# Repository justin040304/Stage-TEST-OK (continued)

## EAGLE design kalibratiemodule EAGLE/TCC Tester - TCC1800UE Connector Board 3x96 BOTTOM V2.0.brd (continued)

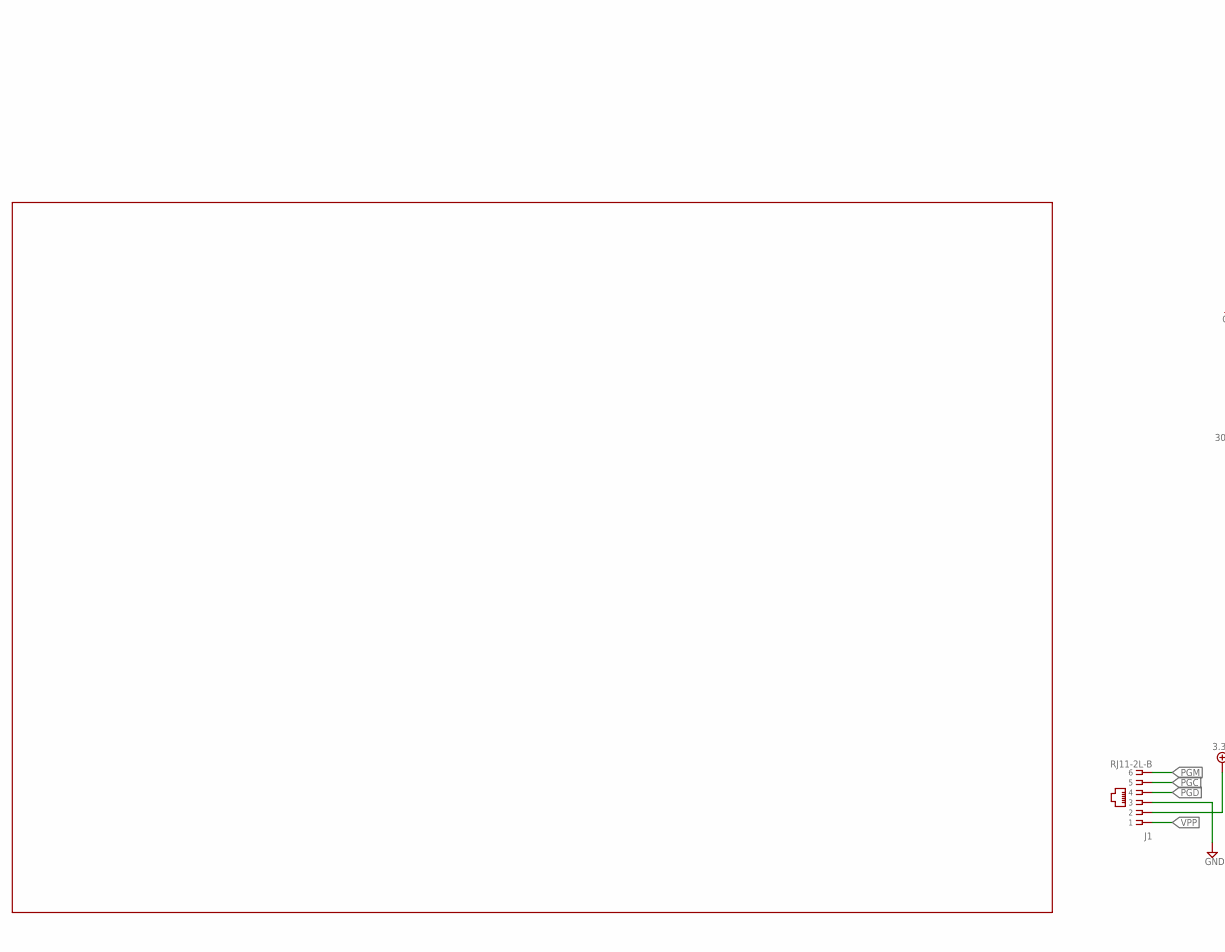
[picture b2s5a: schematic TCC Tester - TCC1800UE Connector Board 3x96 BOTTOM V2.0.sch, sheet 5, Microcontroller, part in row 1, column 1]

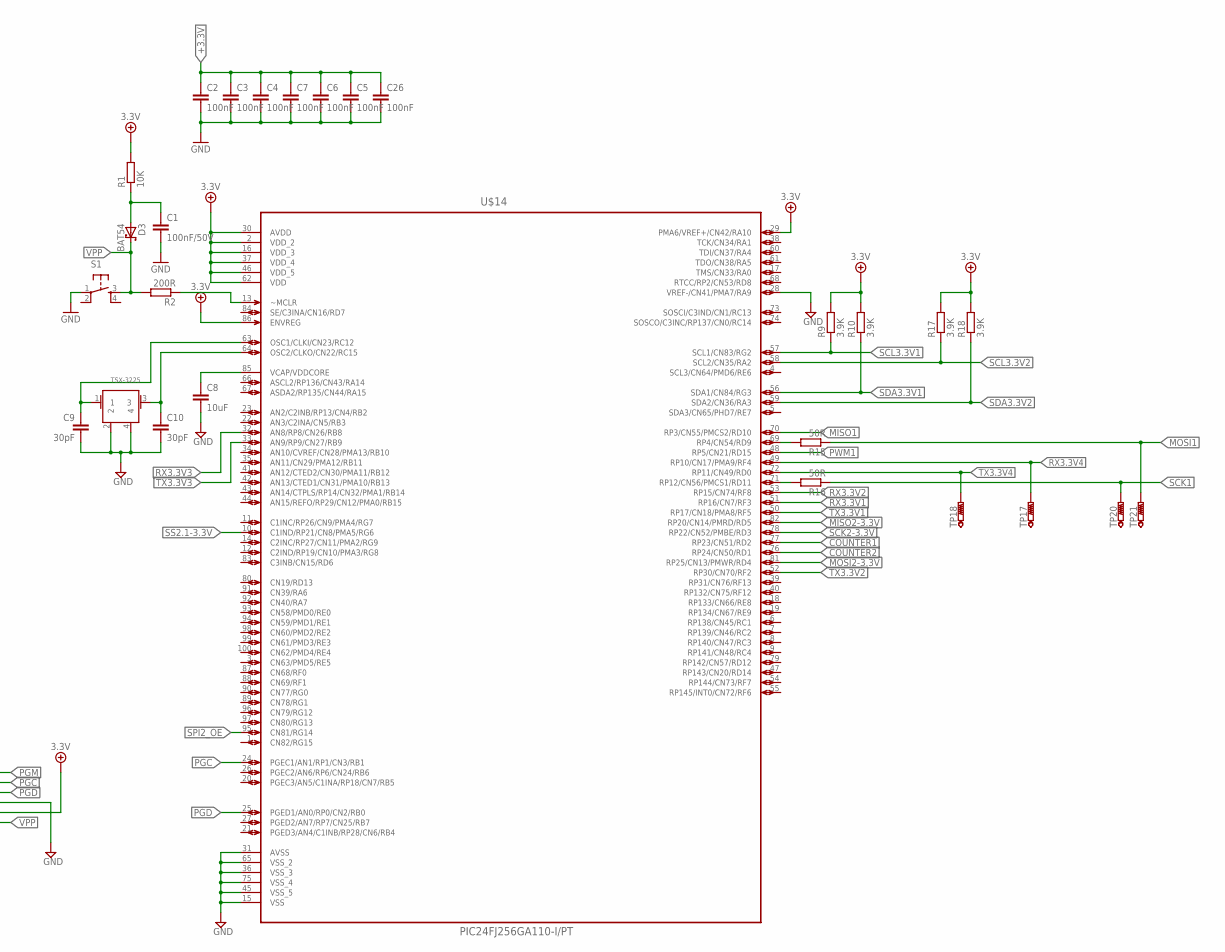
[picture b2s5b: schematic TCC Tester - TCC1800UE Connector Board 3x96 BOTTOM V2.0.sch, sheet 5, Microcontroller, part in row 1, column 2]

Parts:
C1: 100nF/50V; C0603
C2, C3, C4, C5, C6, C7, C26: 100nF; C0603
C8: 10uF; C0603
C9, C10: 30pF; C0603
D3: BAT54; SOT23
J1: RJ11-2L-B; RJ11-NO_SHIELD
R1: 10K; R0603
R2: 200R; R0603
R9, R10, R17, R18: 3.9K; R0603
R15, R16: 50R; R0603
S1: TAC_SWITCHPTH; TACTILE-PTH
TP17, TP18, TP20, TP21: PTR1TP13R; TP13R
U$14: PIC24FJ256GA110-I/PT; QFP40P1400X1400X120-100N
U$15: TSX-3225; SMD,3.2MM_X_2.5MM

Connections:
+3.3V: C2.1, C3.1, C4.1, C5.1, C6.1, C7.1, C26.1, J1.2, R1.2, R9.2, R10.2, R17.2, R18.2, U$14.2 (VDD_2), U$14.16 (VDD_3), U$14.29 (PMA6/VREF+/CN42/RA10), U$14.30 (AVDD), U$14.37 (VDD_4), U$14.46 (VDD_5), U$14.62 (VDD), U$14.86 (ENVREG); also elsewhere on the board
COUNTER1: U$14.77 (RP23/CN51/RD2); also elsewhere on the board
COUNTER2: U$14.76 (RP24/CN50/RD1); also elsewhere on the board
GND: C1.2, C2.2, C3.2, C4.2, C5.2, C6.2, C7.2, C8.2, C9.2, C10.2, C26.2, J1.3, S1.1, U$14.15 (VSS), U$14.28 (VREF-/CN41/PMA7/RA9), U$14.31 (AVSS), U$14.36 (VSS_3), U$14.45 (VSS_5), U$14.65 (VSS_2), U$14.75 (VSS_4), U$15.2, U$15.4; also elsewhere on the board
MISO1: U$14.70 (RP3/CN55/PMCS2/RD10)
MISO2-3.3V: U$14.82 (RP20/CN14/PMRD/RD5); also elsewhere on the board
MOSI1: R15.1, TP21.TP; also elsewhere on the board
MOSI2-3.3V: U$14.81 (RP25/CN13/PMWR/RD4); also elsewhere on the board
unnamed: R15.2, U$14.69 (RP4/CN54/RD9)
unnamed: R16.2, U$14.71 (RP12/CN56/PMCS1/RD11)
unnamed: C1.1, D3.1 (A), R1.1
unnamed: R2.1, U$14.13 (~MCLR)
unnamed: C9.1, U$14.63 (OSC1/CLKI/CN23/RC12), U$15.1
unnamed: C10.1, U$14.64 (OSC2/CLKO/CN22/RC15), U$15.3
unnamed: C8.1, U$14.85 (VCAP/VDDCORE)
PGC: J1.5, U$14.24 (PGEC1/AN1/RP1/CN3/RB1)
PGD: J1.4, U$14.25 (PGED1/AN0/RP0/CN2/RB0)
PGM: J1.6
PWM1: U$14.48 (RP5/CN21/RD15); also elsewhere on the board
RX3.3V1: U$14.51 (RP16/CN7/RF3); also elsewhere on the board
RX3.3V2: U$14.53 (RP15/CN74/RF8); also elsewhere on the board
RX3.3V3: U$14.32 (AN8/RP8/CN26/RB8); also elsewhere on the board
RX3.3V4: TP17.TP, U$14.49 (RP10/CN17/PMA9/RF4)
SCK1: R16.1, TP20.TP; also elsewhere on the board
SCK2-3.3V: U$14.78 (RP22/CN52/PMBE/RD3); also elsewhere on the board
SCL3.3V1: R9.1, U$14.57 (SCL1/CN83/RG2); also elsewhere on the board
SCL3.3V2: R17.1, U$14.58 (SCL2/CN35/RA2); also elsewhere on the board
SDA3.3V1: R10.1, U$14.56 (SDA1/CN84/RG3); also elsewhere on the board
SDA3.3V2: R18.1, U$14.59 (SDA2/CN36/RA3); also elsewhere on the board
SPI2_OE: U$14.95 (CN81/RG14); also elsewhere on the board
SS2.1-3.3V: U$14.10 (C1IND/RP21/CN8/PMA5/RG6); also elsewhere on the board
TX3.3V1: U$14.50 (RP17/CN18/PMA8/RF5); also elsewhere on the board
TX3.3V2: U$14.52 (RP30/CN70/RF2); also elsewhere on the board
TX3.3V3: U$14.33 (AN9/RP9/CN27/RB9); also elsewhere on the board
TX3.3V4: TP18.TP, U$14.72 (RP11/CN49/RD0)
VPP: D3.3 (C), J1.1, R2.2, S1.3

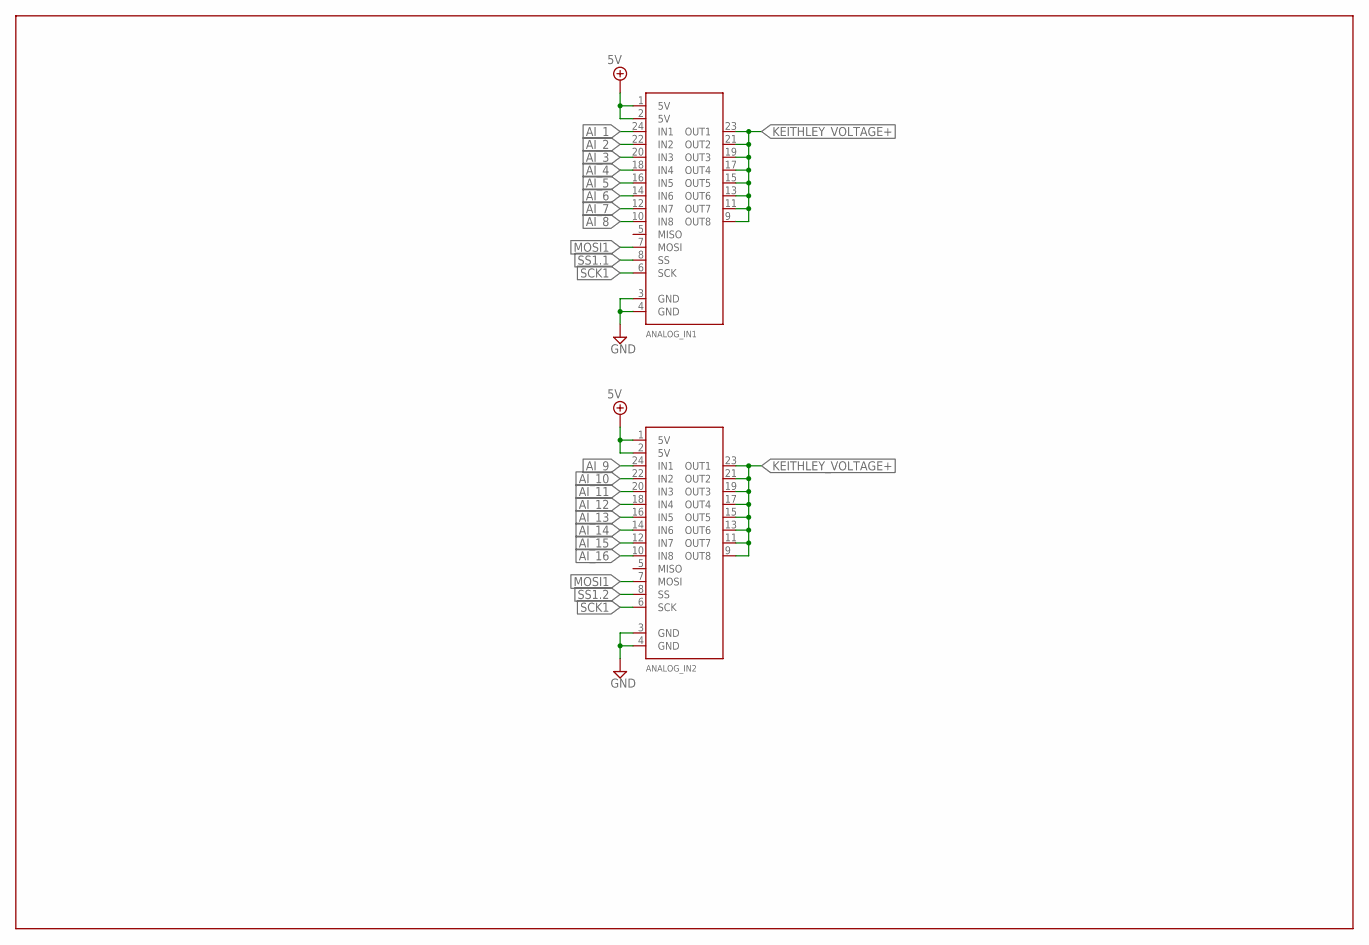
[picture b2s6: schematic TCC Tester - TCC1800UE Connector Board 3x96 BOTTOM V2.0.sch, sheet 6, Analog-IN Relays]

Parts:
ANALOG_IN1, ANALOG_IN2: RELAY_BOARD_SOCKET

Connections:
5V: ANALOG_IN1.1 (5V), ANALOG_IN1.2 (5V), ANALOG_IN2.1 (5V), ANALOG_IN2.2 (5V); also elsewhere on the board
AI_1: ANALOG_IN1.24 (IN1); also elsewhere on the board
AI_2: ANALOG_IN1.22 (IN2); also elsewhere on the board
AI_3: ANALOG_IN1.20 (IN3); also elsewhere on the board
AI_4: ANALOG_IN1.18 (IN4); also elsewhere on the board
AI_5: ANALOG_IN1.16 (IN5); also elsewhere on the board
AI_6: ANALOG_IN1.14 (IN6); also elsewhere on the board
AI_7: ANALOG_IN1.12 (IN7); also elsewhere on the board
AI_8: ANALOG_IN1.10 (IN8); also elsewhere on the board
AI_9: ANALOG_IN2.24 (IN1); also elsewhere on the board
AI_10: ANALOG_IN2.22 (IN2); also elsewhere on the board
AI_11: ANALOG_IN2.20 (IN3); also elsewhere on the board
AI_12: ANALOG_IN2.18 (IN4); also elsewhere on the board
AI_13: ANALOG_IN2.16 (IN5); also elsewhere on the board
AI_14: ANALOG_IN2.14 (IN6); also elsewhere on the board
AI_15: ANALOG_IN2.12 (IN7); also elsewhere on the board
AI_16: ANALOG_IN2.10 (IN8); also elsewhere on the board
GND: ANALOG_IN1.3 (GND), ANALOG_IN1.4 (GND), ANALOG_IN2.3 (GND), ANALOG_IN2.4 (GND); also elsewhere on the board
KEITHLEY_VOLTAGE+: ANALOG_IN1.9 (OUT8), ANALOG_IN1.11 (OUT7), ANALOG_IN1.13 (OUT6), ANALOG_IN1.15 (OUT5), ANALOG_IN1.17 (OUT4), ANALOG_IN1.19 (OUT3), ANALOG_IN1.21 (OUT2), ANALOG_IN1.23 (OUT1), ANALOG_IN2.9 (OUT8), ANALOG_IN2.11 (OUT7), ANALOG_IN2.13 (OUT6), ANALOG_IN2.15 (OUT5), ANALOG_IN2.17 (OUT4), ANALOG_IN2.19 (OUT3), ANALOG_IN2.21 (OUT2), ANALOG_IN2.23 (OUT1); also elsewhere on the board
MOSI1: ANALOG_IN1.7 (MOSI), ANALOG_IN2.7 (MOSI); also elsewhere on the board
SCK1: ANALOG_IN1.6 (SCK), ANALOG_IN2.6 (SCK); also elsewhere on the board
SS1.1: ANALOG_IN1.8 (SS); also elsewhere on the board
SS1.2: ANALOG_IN2.8 (SS); also elsewhere on the board

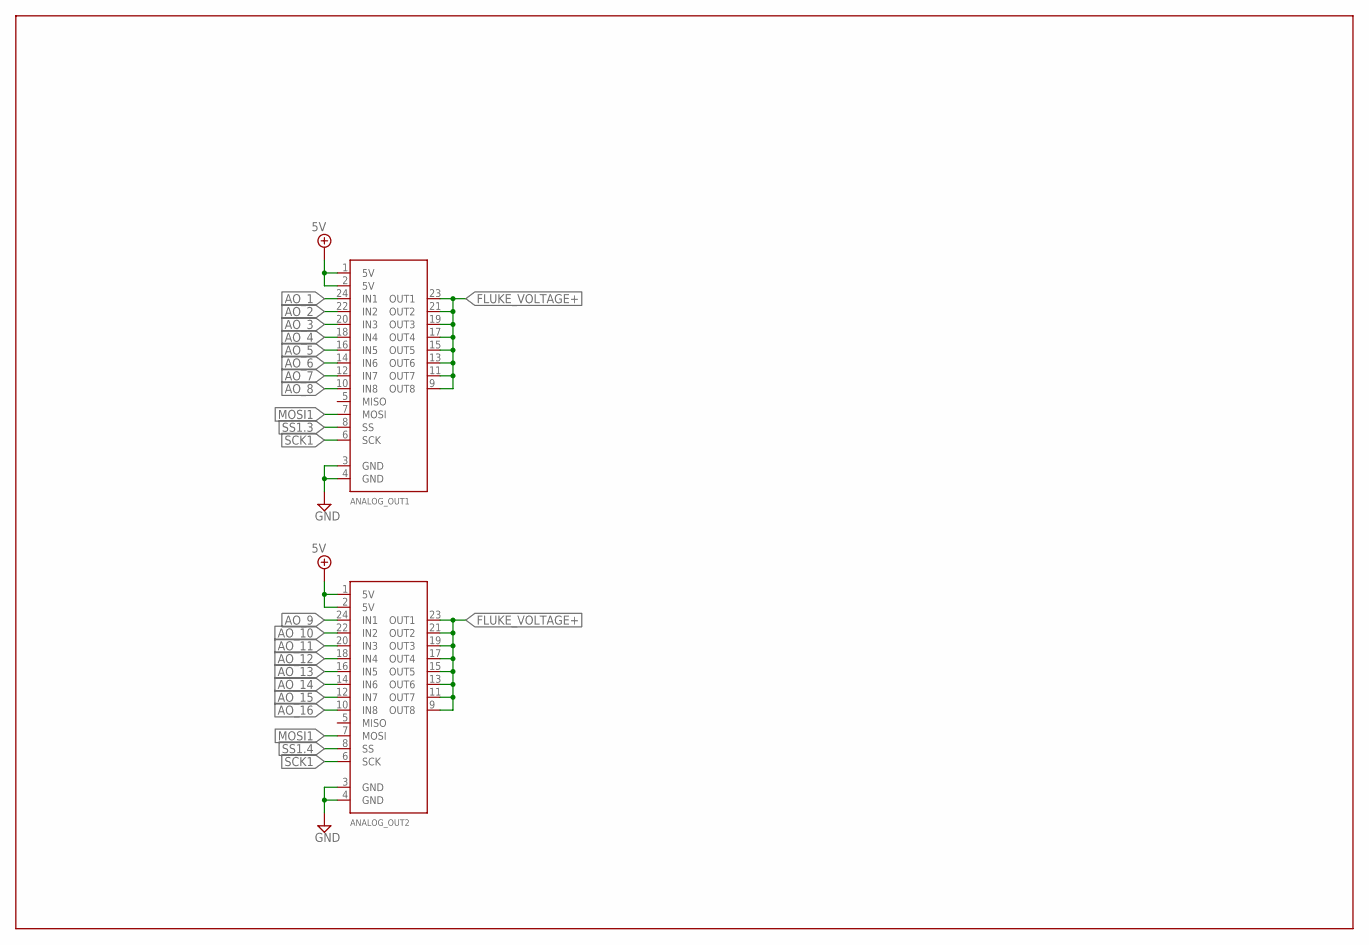
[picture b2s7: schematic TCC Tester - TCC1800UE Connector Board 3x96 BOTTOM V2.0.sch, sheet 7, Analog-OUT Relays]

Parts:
ANALOG_OUT1, ANALOG_OUT2: RELAY_BOARD_SOCKET

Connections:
5V: ANALOG_OUT1.1 (5V), ANALOG_OUT1.2 (5V), ANALOG_OUT2.1 (5V), ANALOG_OUT2.2 (5V); also elsewhere on the board
AO_1: ANALOG_OUT1.24 (IN1); also elsewhere on the board
AO_2: ANALOG_OUT1.22 (IN2); also elsewhere on the board
AO_3: ANALOG_OUT1.20 (IN3); also elsewhere on the board
AO_4: ANALOG_OUT1.18 (IN4); also elsewhere on the board
AO_5: ANALOG_OUT1.16 (IN5); also elsewhere on the board
AO_6: ANALOG_OUT1.14 (IN6); also elsewhere on the board
AO_7: ANALOG_OUT1.12 (IN7); also elsewhere on the board
AO_8: ANALOG_OUT1.10 (IN8); also elsewhere on the board
AO_9: ANALOG_OUT2.24 (IN1); also elsewhere on the board
AO_10: ANALOG_OUT2.22 (IN2); also elsewhere on the board
AO_11: ANALOG_OUT2.20 (IN3); also elsewhere on the board
AO_12: ANALOG_OUT2.18 (IN4); also elsewhere on the board
AO_13: ANALOG_OUT2.16 (IN5); also elsewhere on the board
AO_14: ANALOG_OUT2.14 (IN6); also elsewhere on the board
AO_15: ANALOG_OUT2.12 (IN7); also elsewhere on the board
AO_16: ANALOG_OUT2.10 (IN8); also elsewhere on the board
FLUKE_VOLTAGE+: ANALOG_OUT1.9 (OUT8), ANALOG_OUT1.11 (OUT7), ANALOG_OUT1.13 (OUT6), ANALOG_OUT1.15 (OUT5), ANALOG_OUT1.17 (OUT4), ANALOG_OUT1.19 (OUT3), ANALOG_OUT1.21 (OUT2), ANALOG_OUT1.23 (OUT1), ANALOG_OUT2.9 (OUT8), ANALOG_OUT2.11 (OUT7), ANALOG_OUT2.13 (OUT6), ANALOG_OUT2.15 (OUT5), ANALOG_OUT2.17 (OUT4), ANALOG_OUT2.19 (OUT3), ANALOG_OUT2.21 (OUT2), ANALOG_OUT2.23 (OUT1); also elsewhere on the board
GND: ANALOG_OUT1.3 (GND), ANALOG_OUT1.4 (GND), ANALOG_OUT2.3 (GND), ANALOG_OUT2.4 (GND); also elsewhere on the board
MOSI1: ANALOG_OUT1.7 (MOSI), ANALOG_OUT2.7 (MOSI); also elsewhere on the board
SCK1: ANALOG_OUT1.6 (SCK), ANALOG_OUT2.6 (SCK); also elsewhere on the board
SS1.3: ANALOG_OUT1.8 (SS); also elsewhere on the board
SS1.4: ANALOG_OUT2.8 (SS); also elsewhere on the board

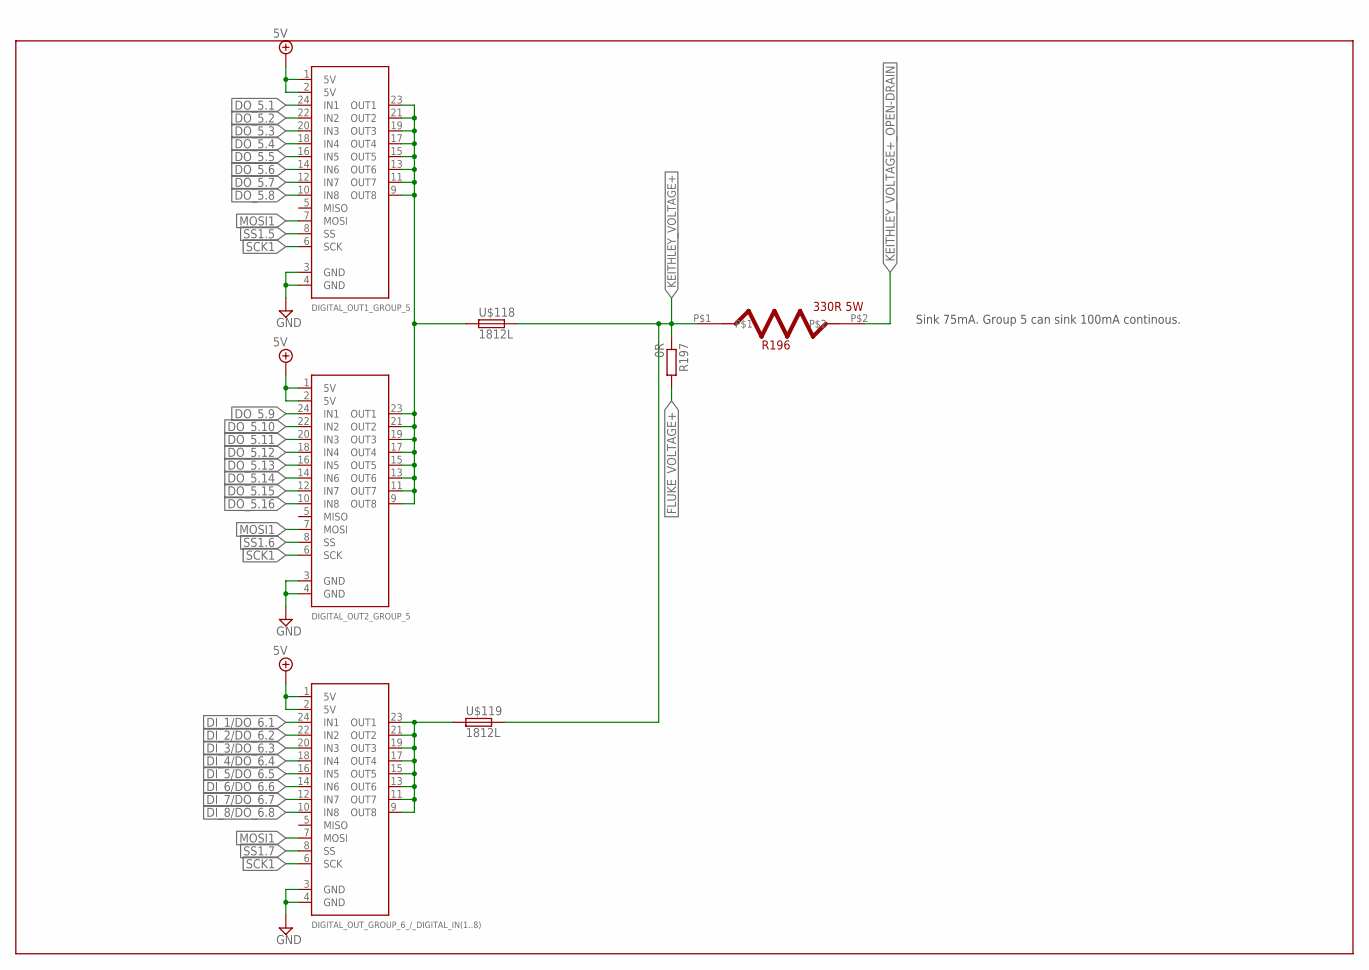
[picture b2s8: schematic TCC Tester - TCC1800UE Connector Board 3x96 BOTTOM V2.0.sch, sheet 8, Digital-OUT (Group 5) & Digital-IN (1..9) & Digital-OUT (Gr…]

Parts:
DIGITAL_OUT1_GROUP_5, DIGITAL_OUT2_GROUP_5: RELAY_BOARD_SOCKET
DIGITAL_OUT_GROUP_6_/_DIGITAL_IN(1..8): RELAY_BOARD_SOCKET
R196: 330R 5W; SMW5220RJT
R197: 0R; R0603
U$118, U$119: 1812L

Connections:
5V: DIGITAL_OUT1_GROUP_5.1 (5V), DIGITAL_OUT1_GROUP_5.2 (5V), DIGITAL_OUT2_GROUP_5.1 (5V), DIGITAL_OUT2_GROUP_5.2 (5V), DIGITAL_OUT_GROUP_6_/_DIGITAL_IN(1..8).1 (5V), DIGITAL_OUT_GROUP_6_/_DIGITAL_IN(1..8).2 (5V); also elsewhere on the board
DI_1/DO_6.1: DIGITAL_OUT_GROUP_6_/_DIGITAL_IN(1..8).24 (IN1); also elsewhere on the board
DI_2/DO_6.2: DIGITAL_OUT_GROUP_6_/_DIGITAL_IN(1..8).22 (IN2); also elsewhere on the board
DI_3/DO_6.3: DIGITAL_OUT_GROUP_6_/_DIGITAL_IN(1..8).20 (IN3); also elsewhere on the board
DI_4/DO_6.4: DIGITAL_OUT_GROUP_6_/_DIGITAL_IN(1..8).18 (IN4); also elsewhere on the board
DI_5/DO_6.5: DIGITAL_OUT_GROUP_6_/_DIGITAL_IN(1..8).16 (IN5); also elsewhere on the board
DI_6/DO_6.6: DIGITAL_OUT_GROUP_6_/_DIGITAL_IN(1..8).14 (IN6); also elsewhere on the board
DI_7/DO_6.7: DIGITAL_OUT_GROUP_6_/_DIGITAL_IN(1..8).12 (IN7); also elsewhere on the board
DI_8/DO_6.8: DIGITAL_OUT_GROUP_6_/_DIGITAL_IN(1..8).10 (IN8); also elsewhere on the board
DO_5.1: DIGITAL_OUT1_GROUP_5.24 (IN1); also elsewhere on the board
DO_5.2: DIGITAL_OUT1_GROUP_5.22 (IN2); also elsewhere on the board
DO_5.3: DIGITAL_OUT1_GROUP_5.20 (IN3); also elsewhere on the board
DO_5.4: DIGITAL_OUT1_GROUP_5.18 (IN4); also elsewhere on the board
DO_5.5: DIGITAL_OUT1_GROUP_5.16 (IN5); also elsewhere on the board
DO_5.6: DIGITAL_OUT1_GROUP_5.14 (IN6); also elsewhere on the board
DO_5.7: DIGITAL_OUT1_GROUP_5.12 (IN7); also elsewhere on the board
DO_5.8: DIGITAL_OUT1_GROUP_5.10 (IN8); also elsewhere on the board
DO_5.9: DIGITAL_OUT2_GROUP_5.24 (IN1); also elsewhere on the board
DO_5.10: DIGITAL_OUT2_GROUP_5.22 (IN2); also elsewhere on the board
DO_5.11: DIGITAL_OUT2_GROUP_5.20 (IN3); also elsewhere on the board
DO_5.12: DIGITAL_OUT2_GROUP_5.18 (IN4); also elsewhere on the board
DO_5.13: DIGITAL_OUT2_GROUP_5.16 (IN5); also elsewhere on the board
DO_5.14: DIGITAL_OUT2_GROUP_5.14 (IN6); also elsewhere on the board
DO_5.15: DIGITAL_OUT2_GROUP_5.12 (IN7); also elsewhere on the board
DO_5.16: DIGITAL_OUT2_GROUP_5.10 (IN8); also elsewhere on the board
FLUKE_VOLTAGE+: R197.2; also elsewhere on the board
GND: DIGITAL_OUT1_GROUP_5.3 (GND), DIGITAL_OUT1_GROUP_5.4 (GND), DIGITAL_OUT2_GROUP_5.3 (GND), DIGITAL_OUT2_GROUP_5.4 (GND), DIGITAL_OUT_GROUP_6_/_DIGITAL_IN(1..8).3 (GND), DIGITAL_OUT_GROUP_6_/_DIGITAL_IN(1..8).4 (GND); also elsewhere on the board
KEITHLEY_VOLTAGE+: R196.P$1, R197.1, U$118.P$2 (2), U$119.P$2 (2); also elsewhere on the board
KEITHLEY_VOLTAGE+_OPEN-DRAIN: R196.P$2; also elsewhere on the board
MOSI1: DIGITAL_OUT1_GROUP_5.7 (MOSI), DIGITAL_OUT2_GROUP_5.7 (MOSI), DIGITAL_OUT_GROUP_6_/_DIGITAL_IN(1..8).7 (MOSI); also elsewhere on the board
unnamed: DIGITAL_OUT1_GROUP_5.9 (OUT8), DIGITAL_OUT1_GROUP_5.11 (OUT7), DIGITAL_OUT1_GROUP_5.13 (OUT6), DIGITAL_OUT1_GROUP_5.15 (OUT5), DIGITAL_OUT1_GROUP_5.17 (OUT4), DIGITAL_OUT1_GROUP_5.19 (OUT3), DIGITAL_OUT1_GROUP_5.21 (OUT2), DIGITAL_OUT1_GROUP_5.23 (OUT1), DIGITAL_OUT2_GROUP_5.9 (OUT8), DIGITAL_OUT2_GROUP_5.11 (OUT7), DIGITAL_OUT2_GROUP_5.13 (OUT6), DIGITAL_OUT2_GROUP_5.15 (OUT5), DIGITAL_OUT2_GROUP_5.17 (OUT4), DIGITAL_OUT2_GROUP_5.19 (OUT3), DIGITAL_OUT2_GROUP_5.21 (OUT2), DIGITAL_OUT2_GROUP_5.23 (OUT1), U$118.P$1 (1)
unnamed: DIGITAL_OUT_GROUP_6_/_DIGITAL_IN(1..8).9 (OUT8), DIGITAL_OUT_GROUP_6_/_DIGITAL_IN(1..8).11 (OUT7), DIGITAL_OUT_GROUP_6_/_DIGITAL_IN(1..8).13 (OUT6), DIGITAL_OUT_GROUP_6_/_DIGITAL_IN(1..8).15 (OUT5), DIGITAL_OUT_GROUP_6_/_DIGITAL_IN(1..8).17 (OUT4), DIGITAL_OUT_GROUP_6_/_DIGITAL_IN(1..8).19 (OUT3), DIGITAL_OUT_GROUP_6_/_DIGITAL_IN(1..8).21 (OUT2), DIGITAL_OUT_GROUP_6_/_DIGITAL_IN(1..8).23 (OUT1), U$119.P$1 (1)
SCK1: DIGITAL_OUT1_GROUP_5.6 (SCK), DIGITAL_OUT2_GROUP_5.6 (SCK), DIGITAL_OUT_GROUP_6_/_DIGITAL_IN(1..8).6 (SCK); also elsewhere on the board
SS1.5: DIGITAL_OUT1_GROUP_5.8 (SS); also elsewhere on the board
SS1.6: DIGITAL_OUT2_GROUP_5.8 (SS); also elsewhere on the board
SS1.7: DIGITAL_OUT_GROUP_6_/_DIGITAL_IN(1..8).8 (SS); also elsewhere on the board

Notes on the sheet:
Sink 75mA. Group 5 can sink 100mA continous.

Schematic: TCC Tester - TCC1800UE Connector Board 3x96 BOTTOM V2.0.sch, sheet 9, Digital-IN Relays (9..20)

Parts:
DIGITAL_IN1, DIGITAL_IN2: RELAY_BOARD_SOCKET

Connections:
5V: DIGITAL_IN1.1 (5V), DIGITAL_IN1.2 (5V), DIGITAL_IN2.1 (5V), DIGITAL_IN2.2 (5V); also elsewhere on the board
DI_9: DIGITAL_IN1.24 (IN1); also elsewhere on the board
DI_10: DIGITAL_IN1.22 (IN2); also elsewhere on the board
DI_11: DIGITAL_IN1.20 (IN3); also elsewhere on the board
DI_12: DIGITAL_IN1.18 (IN4); also elsewhere on the board
DI_13: DIGITAL_IN1.16 (IN5); also elsewhere on the board
DI_14: DIGITAL_IN1.14 (IN6); also elsewhere on the board
DI_15: DIGITAL_IN1.12 (IN7); also elsewhere on the board
DI_16: DIGITAL_IN1.10 (IN8); also elsewhere on the board
DI_17: DIGITAL_IN2.24 (IN1); also elsewhere on the board
DI_18: DIGITAL_IN2.22 (IN2); also elsewhere on the board
DI_19: DIGITAL_IN2.20 (IN3); also elsewhere on the board
DI_20: DIGITAL_IN2.18 (IN4); also elsewhere on the board
GND: DIGITAL_IN1.3 (GND), DIGITAL_IN1.4 (GND), DIGITAL_IN2.3 (GND), DIGITAL_IN2.4 (GND); also elsewhere on the board
KEITHLEY_VOLTAGE+: DIGITAL_IN1.9 (OUT8), DIGITAL_IN1.11 (OUT7), DIGITAL_IN1.13 (OUT6), DIGITAL_IN1.15 (OUT5), DIGITAL_IN1.17 (OUT4), DIGITAL_IN1.19 (OUT3), DIGITAL_IN1.21 (OUT2), DIGITAL_IN1.23 (OUT1), DIGITAL_IN2.17 (OUT4), DIGITAL_IN2.19 (OUT3), DIGITAL_IN2.21 (OUT2), DIGITAL_IN2.23 (OUT1); also elsewhere on the board
MOSI1: DIGITAL_IN1.7 (MOSI), DIGITAL_IN2.7 (MOSI); also elsewhere on the board
SCK1: DIGITAL_IN1.6 (SCK), DIGITAL_IN2.6 (SCK); also elsewhere on the board
SS1.8: DIGITAL_IN1.8 (SS); also elsewhere on the board
SS1.9: DIGITAL_IN2.8 (SS); also elsewhere on the board

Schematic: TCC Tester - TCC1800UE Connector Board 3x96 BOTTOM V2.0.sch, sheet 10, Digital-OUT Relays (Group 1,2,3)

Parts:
DIGITAL_OUT_GROUP_1, DIGITAL_OUT_GROUP_2, DIGITAL_OUT_GROUP_3: RELAY_BOARD_SOCKET
R12, R13, R14: 100R 500mW; R0805

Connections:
5V: DIGITAL_OUT_GROUP_1.1 (5V), DIGITAL_OUT_GROUP_1.2 (5V), DIGITAL_OUT_GROUP_2.1 (5V), DIGITAL_OUT_GROUP_2.2 (5V), DIGITAL_OUT_GROUP_3.1 (5V), DIGITAL_OUT_GROUP_3.2 (5V); also elsewhere on the board
DO_1.1: DIGITAL_OUT_GROUP_1.24 (IN1); also elsewhere on the board
DO_1.2: DIGITAL_OUT_GROUP_1.22 (IN2); also elsewhere on the board
DO_1.3: DIGITAL_OUT_GROUP_1.20 (IN3); also elsewhere on the board
DO_1.4: DIGITAL_OUT_GROUP_1.18 (IN4); also elsewhere on the board
DO_1.5: DIGITAL_OUT_GROUP_1.16 (IN5); also elsewhere on the board
DO_1.6: DIGITAL_OUT_GROUP_1.14 (IN6); also elsewhere on the board
DO_1.7: DIGITAL_OUT_GROUP_1.12 (IN7); also elsewhere on the board
DO_1.8: DIGITAL_OUT_GROUP_1.10 (IN8); also elsewhere on the board
DO_2.1: DIGITAL_OUT_GROUP_2.24 (IN1); also elsewhere on the board
DO_2.2: DIGITAL_OUT_GROUP_2.22 (IN2); also elsewhere on the board
DO_2.3: DIGITAL_OUT_GROUP_2.20 (IN3); also elsewhere on the board
DO_2.4: DIGITAL_OUT_GROUP_2.18 (IN4); also elsewhere on the board
DO_2.5: DIGITAL_OUT_GROUP_2.16 (IN5); also elsewhere on the board
DO_2.6: DIGITAL_OUT_GROUP_2.14 (IN6); also elsewhere on the board
DO_2.7: DIGITAL_OUT_GROUP_2.12 (IN7); also elsewhere on the board
DO_2.8: DIGITAL_OUT_GROUP_2.10 (IN8); also elsewhere on the board
DO_3.1: DIGITAL_OUT_GROUP_3.24 (IN1); also elsewhere on the board
DO_3.2: DIGITAL_OUT_GROUP_3.22 (IN2); also elsewhere on the board
DO_3.3: DIGITAL_OUT_GROUP_3.20 (IN3); also elsewhere on the board
DO_3.4: DIGITAL_OUT_GROUP_3.18 (IN4); also elsewhere on the board
DO_3.5: DIGITAL_OUT_GROUP_3.16 (IN5); also elsewhere on the board
DO_3.6: DIGITAL_OUT_GROUP_3.14 (IN6); also elsewhere on the board
DO_3.7: DIGITAL_OUT_GROUP_3.12 (IN7); also elsewhere on the board
DO_3.8: DIGITAL_OUT_GROUP_3.10 (IN8); also elsewhere on the board
FLUKE_VOLTAGE+: R12.2, R13.2, R14.2; also elsewhere on the board
GND: DIGITAL_OUT_GROUP_1.3 (GND), DIGITAL_OUT_GROUP_1.4 (GND), DIGITAL_OUT_GROUP_2.3 (GND), DIGITAL_OUT_GROUP_2.4 (GND), DIGITAL_OUT_GROUP_3.3 (GND), DIGITAL_OUT_GROUP_3.4 (GND); also elsewhere on the board
MOSI1: DIGITAL_OUT_GROUP_1.7 (MOSI), DIGITAL_OUT_GROUP_2.7 (MOSI), DIGITAL_OUT_GROUP_3.7 (MOSI); also elsewhere on the board
unnamed: DIGITAL_OUT_GROUP_1.9 (OUT8), DIGITAL_OUT_GROUP_1.11 (OUT7), DIGITAL_OUT_GROUP_1.13 (OUT6), DIGITAL_OUT_GROUP_1.15 (OUT5), DIGITAL_OUT_GROUP_1.17 (OUT4), DIGITAL_OUT_GROUP_1.19 (OUT3), DIGITAL_OUT_GROUP_1.21 (OUT2), DIGITAL_OUT_GROUP_1.23 (OUT1), R12.1
unnamed: DIGITAL_OUT_GROUP_2.9 (OUT8), DIGITAL_OUT_GROUP_2.11 (OUT7), DIGITAL_OUT_GROUP_2.13 (OUT6), DIGITAL_OUT_GROUP_2.15 (OUT5), DIGITAL_OUT_GROUP_2.17 (OUT4), DIGITAL_OUT_GROUP_2.19 (OUT3), DIGITAL_OUT_GROUP_2.21 (OUT2), DIGITAL_OUT_GROUP_2.23 (OUT1), R13.1
unnamed: DIGITAL_OUT_GROUP_3.9 (OUT8), DIGITAL_OUT_GROUP_3.11 (OUT7), DIGITAL_OUT_GROUP_3.13 (OUT6), DIGITAL_OUT_GROUP_3.15 (OUT5), DIGITAL_OUT_GROUP_3.17 (OUT4), DIGITAL_OUT_GROUP_3.19 (OUT3), DIGITAL_OUT_GROUP_3.21 (OUT2), DIGITAL_OUT_GROUP_3.23 (OUT1), R14.1
SCK1: DIGITAL_OUT_GROUP_1.6 (SCK), DIGITAL_OUT_GROUP_2.6 (SCK), DIGITAL_OUT_GROUP_3.6 (SCK); also elsewhere on the board
SS1.10: DIGITAL_OUT_GROUP_1.8 (SS); also elsewhere on the board
SS1.11: DIGITAL_OUT_GROUP_2.8 (SS); also elsewhere on the board
SS1.12: DIGITAL_OUT_GROUP_3.8 (SS); also elsewhere on the board

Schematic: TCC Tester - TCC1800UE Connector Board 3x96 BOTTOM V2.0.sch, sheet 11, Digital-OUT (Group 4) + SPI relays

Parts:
DIGITAL_OUT_GROUP_4: RELAY_BOARD_SOCKET
R21, R25, R27, R28, R29, R31: 100R; R0603
U$24, U$36: ESDA5V3L; SOT23

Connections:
5V: DIGITAL_OUT_GROUP_4.1 (5V), DIGITAL_OUT_GROUP_4.2 (5V); also elsewhere on the board
$234: DIGITAL_OUT_GROUP_4.13 (OUT6), R25.1
$355: DIGITAL_OUT_GROUP_4.15 (OUT5), R21.1
$24323: DIGITAL_OUT_GROUP_4.9 (OUT8), R28.1
$345345: DIGITAL_OUT_GROUP_4.11 (OUT7), R27.1
DI_9: R21.2; also elsewhere on the board
DO_1.1: R27.2; also elsewhere on the board
DO_1.2: R25.2; also elsewhere on the board
DO_1.3: R28.2; also elsewhere on the board
DO_4.1: DIGITAL_OUT_GROUP_4.24 (IN1); also elsewhere on the board
DO_4.2: DIGITAL_OUT_GROUP_4.22 (IN2); also elsewhere on the board
DO_4.3: DIGITAL_OUT_GROUP_4.20 (IN3); also elsewhere on the board
DO_4.4: DIGITAL_OUT_GROUP_4.18 (IN4); also elsewhere on the board
FLUKE_VOLTAGE+: DIGITAL_OUT_GROUP_4.17 (OUT4), DIGITAL_OUT_GROUP_4.19 (OUT3), DIGITAL_OUT_GROUP_4.21 (OUT2), DIGITAL_OUT_GROUP_4.23 (OUT1); also elsewhere on the board
GND: DIGITAL_OUT_GROUP_4.3 (GND), DIGITAL_OUT_GROUP_4.4 (GND), R29.1, R31.1; also elsewhere on the board
MISO2-5V: DIGITAL_OUT_GROUP_4.16 (IN5), U$36.1 (C1); also elsewhere on the board
MOSI1: DIGITAL_OUT_GROUP_4.7 (MOSI); also elsewhere on the board
MOSI2-5V: DIGITAL_OUT_GROUP_4.14 (IN6), U$36.2 (C2); also elsewhere on the board
unnamed: R29.2, U$24.3 (A)
unnamed: R31.2, U$36.3 (A)
SCK1: DIGITAL_OUT_GROUP_4.6 (SCK); also elsewhere on the board
SCK2-5V: DIGITAL_OUT_GROUP_4.12 (IN7), U$24.1 (C1); also elsewhere on the board
SS1.13: DIGITAL_OUT_GROUP_4.8 (SS); also elsewhere on the board
SS2.1-5V: DIGITAL_OUT_GROUP_4.10 (IN8), U$24.2 (C2); also elsewhere on the board

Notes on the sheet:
SPI TCC
MISO
MOSI
SCK

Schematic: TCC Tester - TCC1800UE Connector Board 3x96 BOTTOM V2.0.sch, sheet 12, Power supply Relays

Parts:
C42: 100nF; C0603
LED106, LED107, LED108, LED109, LED110, LED111, LED112, LED113: LEDCHIPLED_0805; CHIPLED_0805
R152, R153, R154, R155, R156, R157, R158, R159: 2.2K; R0603
R173: 0R; R0603
R_SUPPLY1, R_SUPPLY2, R_SUPPLY24VAC_1A, R_SUPPLY24VAC_1B, R_SUPPLY24VAC_2A, R_SUPPLY24VAC_2B: RELAY-SPDT; SPDT_TE_PE014*
R_SUPPLY+5V, R_SUPPLY+26V: RELAY-SPDT; SPDT_TE_PE014*
U$25: MAX4820; TSSOP20

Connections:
5V: C42.1, LED106.A, LED107.A, LED108.A, LED109.A, LED110.A, LED111.A, LED112.A, LED113.A, R173.1, R_SUPPLY1.1 (A1), R_SUPPLY2.1 (A1), R_SUPPLY24VAC_1A.1 (A1), R_SUPPLY24VAC_1B.1 (A1), R_SUPPLY24VAC_2A.1 (A1), R_SUPPLY24VAC_2B.1 (A1), R_SUPPLY+5V.1 (A1), R_SUPPLY+26V.1 (A1), U$25.1 (VCC), U$25.15 (COM); also elsewhere on the board
24VAC_1A: R_SUPPLY24VAC_1A.11; also elsewhere on the board
24VAC_1B: R_SUPPLY24VAC_1B.11; also elsewhere on the board
24VAC_2A: R_SUPPLY24VAC_2A.11; also elsewhere on the board
24VAC_2B: R_SUPPLY24VAC_2B.11; also elsewhere on the board
+5V_TCC: R_SUPPLY+5V.11; also elsewhere on the board
+26V_UNREGULATED: R_SUPPLY+26V.11; also elsewhere on the board
FLUKE_COMMON1: R_SUPPLY24VAC_1B.14, R_SUPPLY24VAC_2B.14; also elsewhere on the board
FLUKE_VOLTAGE+: R_SUPPLY1.14, R_SUPPLY2.14, R_SUPPLY24VAC_1A.14, R_SUPPLY24VAC_2A.14, R_SUPPLY+5V.14, R_SUPPLY+26V.14; also elsewhere on the board
GND: C42.2, U$25.9 (GND), U$25.12 (PGND), U$25.18 (PGND); also elsewhere on the board
MOSI1: U$25.5 (DIN); also elsewhere on the board
unnamed: R157.2, R_SUPPLY24VAC_1B.2 (A2), U$25.13 (OUT6)
unnamed: R154.2, R_SUPPLY+26V.2 (A2), U$25.17 (OUT3)
unnamed: R155.2, R_SUPPLY+5V.2 (A2), U$25.16 (OUT4)
unnamed: R156.2, R_SUPPLY24VAC_1A.2 (A2), U$25.14 (OUT5)
unnamed: R152.2, R_SUPPLY1.2 (A2), U$25.20 (OUT1)
unnamed: R153.2, R_SUPPLY2.2 (A2), U$25.19 (OUT2)
unnamed: R158.2, R_SUPPLY24VAC_2A.2 (A2), U$25.11 (OUT7)
unnamed: R159.2, R_SUPPLY24VAC_2B.2 (A2), U$25.10 (OUT8)
unnamed: R173.2, U$25.2 (SET), U$25.3 (RESET)
unnamed: LED106.C, R152.1
unnamed: LED107.C, R153.1
unnamed: LED108.C, R154.1
unnamed: LED109.C, R155.1
unnamed: LED110.C, R156.1
unnamed: LED111.C, R157.1
unnamed: LED112.C, R158.1
unnamed: LED113.C, R159.1
SCK1: U$25.6 (CLK); also elsewhere on the board
SS1.14: U$25.4 (CS); also elsewhere on the board
SUPPLY_1: R_SUPPLY1.11; also elsewhere on the board
SUPPLY_2: R_SUPPLY2.11; also elsewhere on the board

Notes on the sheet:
VOLTAGE AND CURRENT MEASUREMENTS OF THE POWER SUPPLIES

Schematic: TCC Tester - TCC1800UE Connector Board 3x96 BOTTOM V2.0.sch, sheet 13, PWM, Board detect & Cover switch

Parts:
C19: 100nF; C0603
PWM_COVERSWITCH_BOARDDETECT: RELAY_BOARD_SOCKET
SW1: SPDT; APEM25136N
U8: SN74AHCT1G125DCKT; SOT65P210X110-5N

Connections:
5V: C19.1, PWM_COVERSWITCH_BOARDDETECT.1 (5V), PWM_COVERSWITCH_BOARDDETECT.2 (5V), U8.5 (VCC); also elsewhere on the board
BOARD_DETECT: SW1.COM (COMMON); also elsewhere on the board
COVER_RELAY: PWM_COVERSWITCH_BOARDDETECT.11 (OUT7); also elsewhere on the board
DI_1/DO_6.1: PWM_COVERSWITCH_BOARDDETECT.24 (IN1); also elsewhere on the board
DI_2/DO_6.2: PWM_COVERSWITCH_BOARDDETECT.22 (IN2); also elsewhere on the board
DI_3/DO_6.3: PWM_COVERSWITCH_BOARDDETECT.20 (IN3); also elsewhere on the board
DI_4/DO_6.4: PWM_COVERSWITCH_BOARDDETECT.18 (IN4); also elsewhere on the board
DI_5/DO_6.5: PWM_COVERSWITCH_BOARDDETECT.16 (IN5); also elsewhere on the board
D_+26V: PWM_COVERSWITCH_BOARDDETECT.12 (IN7); also elsewhere on the board
GND: C19.2, PWM_COVERSWITCH_BOARDDETECT.3 (GND), PWM_COVERSWITCH_BOARDDETECT.4 (GND), SW1.S1 (NC), U8.1 (~OE), U8.3 (GND); also elsewhere on the board
MOSI1: PWM_COVERSWITCH_BOARDDETECT.7 (MOSI); also elsewhere on the board
PWM1: U8.2 (A); also elsewhere on the board
PWM1_OUT: PWM_COVERSWITCH_BOARDDETECT.15 (OUT5), PWM_COVERSWITCH_BOARDDETECT.17 (OUT4), PWM_COVERSWITCH_BOARDDETECT.19 (OUT3), PWM_COVERSWITCH_BOARDDETECT.21 (OUT2), PWM_COVERSWITCH_BOARDDETECT.23 (OUT1), U8.4 (Y)
SCK1: PWM_COVERSWITCH_BOARDDETECT.6 (SCK); also elsewhere on the board
SS1.15: PWM_COVERSWITCH_BOARDDETECT.8 (SS); also elsewhere on the board

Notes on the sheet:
Cover Switch
Switch for Board Detect

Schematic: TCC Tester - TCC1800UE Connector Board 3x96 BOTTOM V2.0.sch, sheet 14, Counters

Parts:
C22, C23: 100nF; C0603
U$80, U$82: SN74LV1T34; SOT23-5

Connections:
+3.3V: C22.1, C23.1, U$80.5 (VCC), U$82.5 (VCC); also elsewhere on the board
COUNTER1: U$80.4 (Y); also elsewhere on the board
COUNTER2: U$82.4 (Y); also elsewhere on the board
GND: C22.2, C23.2, U$80.3 (GND), U$82.3 (GND); also elsewhere on the board
PWM_1: U$80.2 (A); also elsewhere on the board
PWM_2: U$82.2 (A); also elsewhere on the board

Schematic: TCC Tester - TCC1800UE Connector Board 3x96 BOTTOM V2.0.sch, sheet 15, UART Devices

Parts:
C11, C12: 10nF/250V; C050-050X075
C18: 3u3/25V; SMC_A
C24, C25, C27, C28, C29, C43: 100nF; C0603
C44: 10uF; EIA3216
CN6: USB_CONNECTORTYCO; TYCO_USB_B
CN7: TYCO_1-406541-1_RJ45_TAB_UP; TYCO_1-406541-1
D1, D2: ORANGE; LED-0603
JP3, JP4: JP2E; JP2
L2: 40R; R0805
R32, R33: 100R; R0603
R176, R177: 270R; R0603
R180: 0R; R0603
R181: 0R DNP; R0603
U7, U9: TXS0102DCUR; SOP50P310X90-8N
U10: FT232RLSSOP; SSOP28DB
XP1: XPORT

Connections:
5V: C24.1, C27.1, R176.2, R177.2, R180.2, U7.7 (VCCB), U9.7 (VCCB); also elsewhere on the board
+3.3V: C11.1, C18.+, C25.1, C28.1, C29.1, U7.3 (VCCA), U7.6 (OE), U9.3 (VCCA), U9.6 (OE), XP1.2 (VCC); also elsewhere on the board
ETH_RX_N: CN7.2 (7); also elsewhere on the board
ETH_RX_P: CN7.1 (8); also elsewhere on the board
ETH_TX_N: CN7.6 (3); also elsewhere on the board
ETH_TX_P: CN7.4 (5); also elsewhere on the board
GND: C12.2, C18.-, C24.2, C25.2, C27.2, C28.2, C29.2, C43.2, C44.C (-), CN6.4 (GND), CN6.SHIELD@1 (SHIELD), CN6.SHIELD@2 (SHIELD), CN7.SHIELD (S), CN7.SHIELD1 (S), U7.2 (GND), U9.2 (GND), U10.7 (GND7), U10.18 (GND18), U10.21 (GND21), U10.25 (AGND), U10.26 (TEST), XP1.1 (GND); also elsewhere on the board
unnamed: C11.2, C12.1, XP1.SH1 (SH), XP1.SH2 (SH)
unnamed: R33.1, XP1.5 (IN)
unnamed: CN6.3 (D+), U10.15 (USBDP)
unnamed: C43.1, L2.1, R180.1, R181.1
unnamed: D1.C, U10.23 (TXLED)
unnamed: D2.C, U10.22 (RXLED)
unnamed: CN6.2 (D-), U10.16 (USBDM)
unnamed: D1.A, R176.1
unnamed: D2.A, R177.1
unnamed: C44.A (+), L2.2, U10.4 (VCCIO), U10.20 (VCC)
unnamed: CN6.1 (VBUS), R181.2
unnamed: R32.1, XP1.4 (OUT)
RX3.3V1: JP3.2; also elsewhere on the board
RX3.3V1.1: JP3.3, R32.2
RX3.3V1.2: JP3.1, U9.5 (A1)
RX3.3V3: U7.5 (A1); also elsewhere on the board
RX5V1.2: U9.8 (B1), U10.1 (TXD)
SERIAL_RX: U7.1 (B2); also elsewhere on the board
SERIAL_TX: U7.8 (B1); also elsewhere on the board
TX3.3V1: JP4.2; also elsewhere on the board
TX3.3V1.1: JP4.3, R33.2
TX3.3V1.2: JP4.1, U9.4 (A2)
TX3.3V3: U7.4 (A2); also elsewhere on the board
TX5V1.2: U9.1 (B2), U10.5 (RXD)

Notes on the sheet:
UART Level shifter for UART test
UART Level shifter for Microcontroller communication with TEST-TRACK
USB TO UART FOR USB COMMUNICATION WITH TEST-TRACK
Place both jumpers for UART communication via FTDI. If jumpers are not placed, the UART communication works via the XPORT

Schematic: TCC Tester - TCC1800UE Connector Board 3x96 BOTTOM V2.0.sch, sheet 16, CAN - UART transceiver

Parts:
C14: 100nF; C0603
R3: 120R; R0603
R4: 0R; R0603
U4: MAX3051ESAESA+; SO8

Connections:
+3.3V: C14.1, U4.3 (VCC); also elsewhere on the board
CANH: R3.2, U4.7 (CANH); also elsewhere on the board
CANL: R3.1, U4.6 (CANL); also elsewhere on the board
GND: C14.2, R4.2, U4.2 (GND); also elsewhere on the board
unnamed: R4.1, U4.8 (RS)
RX3.3V2: U4.1 (TXD); also elsewhere on the board
TX3.3V2: U4.4 (RXD); also elsewhere on the board

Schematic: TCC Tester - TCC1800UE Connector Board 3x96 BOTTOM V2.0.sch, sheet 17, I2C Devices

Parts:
C15, C16, C17: 100nF; C0603
JP1: JP2E; JP2
JP2: JP3Q
R5, R7, R8: 4.7K; R0603
R6: 4.7K DNP; R0603
U3: AT24C04C-SSHM-T; SOIC127P600X175-8N
U5: TCA9406DCTR; SOP65P400X130-8N

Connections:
5V: C17.1, R5.2, R6.2, U5.7 (VCCB); also elsewhere on the board
+3.3V: C15.1, C16.1, JP2.6, R7.2, R8.2, U3.2 (A1/NC), U3.3 (A2), U3.8 (VCC), U5.3 (VCCA), U5.6 (OE); also elsewhere on the board
GND: C15.2, C16.2, C17.2, JP2.2, U3.4 (GND), U5.2 (GND); also elsewhere on the board
I2C_3.3SCL: JP1.3, R7.1, U5.5 (SCL_A)
I2C_3.3SDA: JP2.5, R8.1, U5.4 (SDA_A)
I2C_SCL: R5.1, U5.8 (SCL_B); also elsewhere on the board
I2C_SDA: R6.1, U5.1 (SDA_B); also elsewhere on the board
unnamed: JP1.2, U3.6 (SCL)
unnamed: JP2.3, U3.5 (SDA)
SCL3.3V2: JP1.1; also elsewhere on the board
SDA3.3V2: JP2.1; also elsewhere on the board
WP_EEPROM: JP2.4, U3.7 (WP)

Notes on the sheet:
For programming eeprom
For Reading eeprom
